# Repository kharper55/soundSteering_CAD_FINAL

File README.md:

All CAD pdfs and RAW files from KiCAD6 and some nice pin mapping references + block diagrams. Custom symbol and footprint library (not provided) needed to rebuild Gerbers (provided as-is). 

Contains schematic, PCB, BOM (entire KiCAD project + PDF prints) and Gerber files for 3x 4 layer mixed signal PCBs. KiCAD project has since seen edits in silkscreen and rectifying some issues with DNP parts.

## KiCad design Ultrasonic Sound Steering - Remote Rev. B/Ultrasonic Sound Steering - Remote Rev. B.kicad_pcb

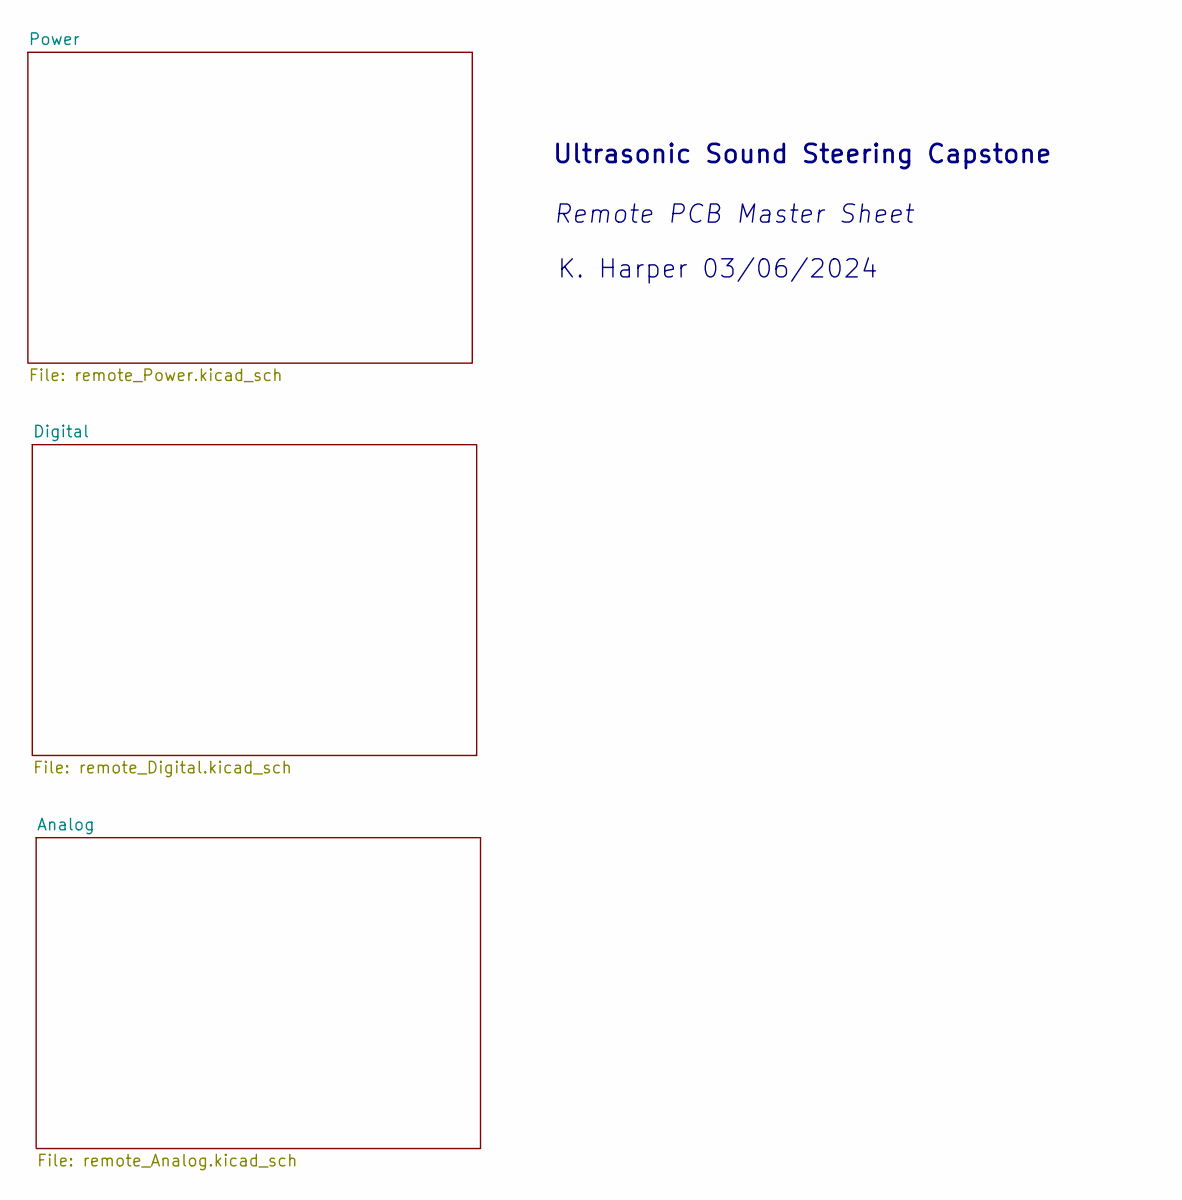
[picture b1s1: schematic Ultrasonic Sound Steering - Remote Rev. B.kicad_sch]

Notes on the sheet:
Remote PCB Master Sheet
K. Harper 03/06/2024
Ultrasonic Sound Steering Capstone

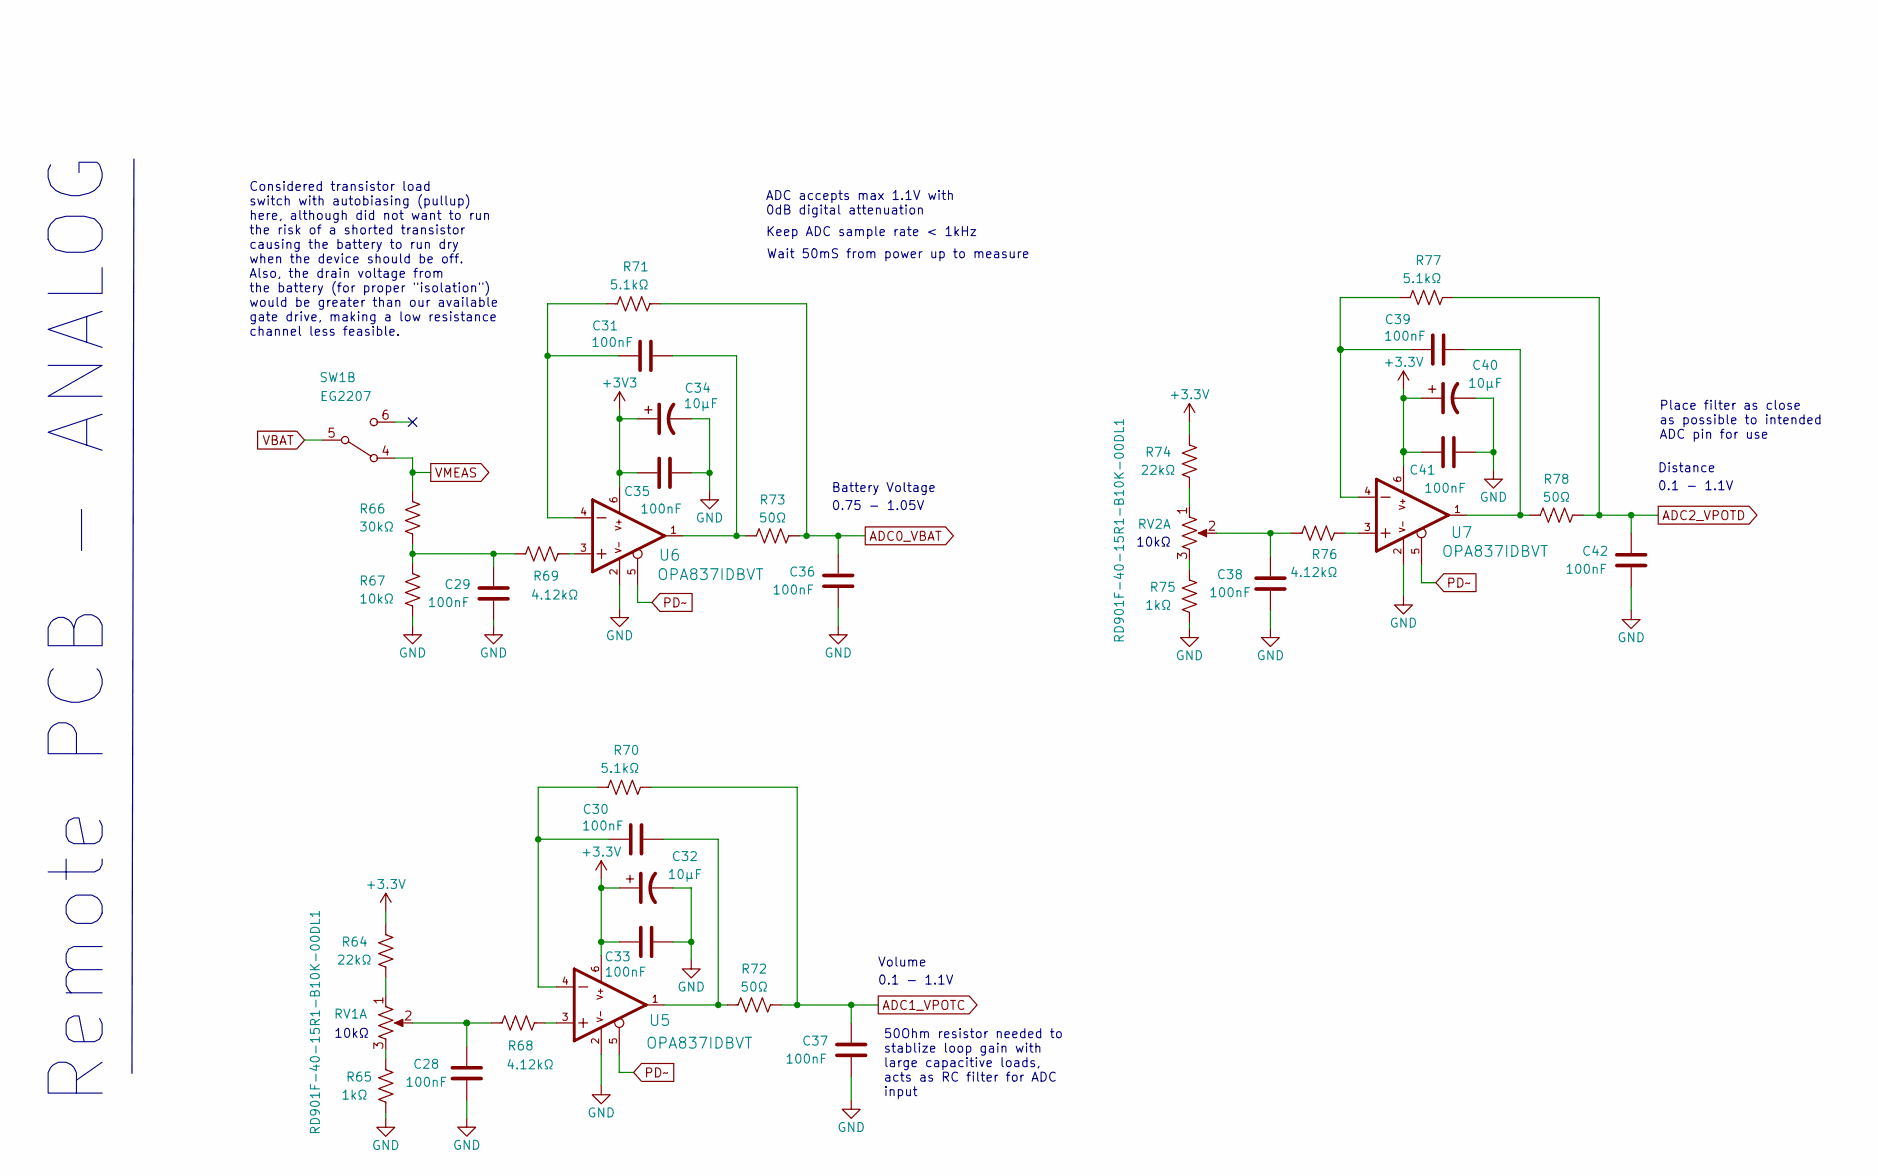
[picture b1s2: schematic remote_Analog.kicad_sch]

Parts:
C28, C29, C30, C31, C33, C35, C36, C37, C38, C39, C41, C42: 100nF; C_0603_1608Metric
C32, C34, C40: 10µF; C_TANT_1608-10
R64, R74: 22kΩ; R_0603_1608Metric
R65, R75: 1kΩ; R_0603_1608Metric
R66: 30kΩ; R_0603_1608Metric
R67: 10kΩ; R_0603_1608Metric
R68, R69, R76: 4.12kΩ; R_0603_1608Metric
R70, R71, R77: 5.1kΩ; R_0603_1608Metric
R72, R73, R78: 50Ω; R_0603_1608Metric
RV1, RV2: RD901F-40-15R1-B10K-00DL1; Potentiometer_Alps_RK09L_Single_Vertical
SW1: EG2207; SW_EG2207
U5, U6, U7: OPA837IDBVT; IC_SOT23-6

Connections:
ADC1_VPOTC: C37.2, R70.2, R72.2; also elsewhere on the board
ADC2_VPOTD: C42.2, R77.2, R78.2; also elsewhere on the board
GND: C28.1, C29.1, C32.2, C33.2, C34.2, C35.2, C36.1, C37.1, C38.1, C40.2, C41.2, C42.1, R65.2, R67.2, R75.2, U5.2, U6.2, U7.2; also elsewhere on the board
unnamed: C28.2, R68.1, RV1.2
unnamed: C29.2, R66.2, R67.1, R69.1
unnamed: C30.1, R70.1, U5.4
unnamed: C30.2, R72.1, U5.1
unnamed: C31.1, R71.1, U6.4
unnamed: C31.2, R73.1, U6.1
unnamed: C38.2, R76.1, RV2.2
unnamed: C39.1, R77.1, U7.4
unnamed: C39.2, R78.1, U7.1
unnamed: R64.2, RV1.1
unnamed: R65.1, RV1.3
unnamed: R68.2, U5.3
unnamed: R69.2, U6.3
unnamed: R74.2, RV2.1
unnamed: R75.1, RV2.3
unnamed: R76.2, U7.3
PD~: U5.5, U6.5, U7.5; also elsewhere on the board
VBAT: SW1.5; also elsewhere on the board
VMEAS: R66.1, SW1.4; also elsewhere on the board

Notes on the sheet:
Wait 50mS from power up to measure
Distance
Remote PCB - ANALOG
Place filter as close as possible to intended ADC pin for use
0.75 - 1.05V
Keep ADC sample rate < 1kHz
ADC accepts max 1.1V with 0dB digital attenuation
Volume
50Ohm resistor needed to stablize loop gain with large capacitive loads, acts as RC filter for ADC input
10kΩ
Battery Voltage
0.1 - 1.1V
Considered transistor load switch with autobiasing (pullup) here, although did not want to run the risk of a shorted transistor causing the battery to run dry when the device should be off. Also, the drain voltage from the battery (for proper "isolation") would be greater than our available gate dr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

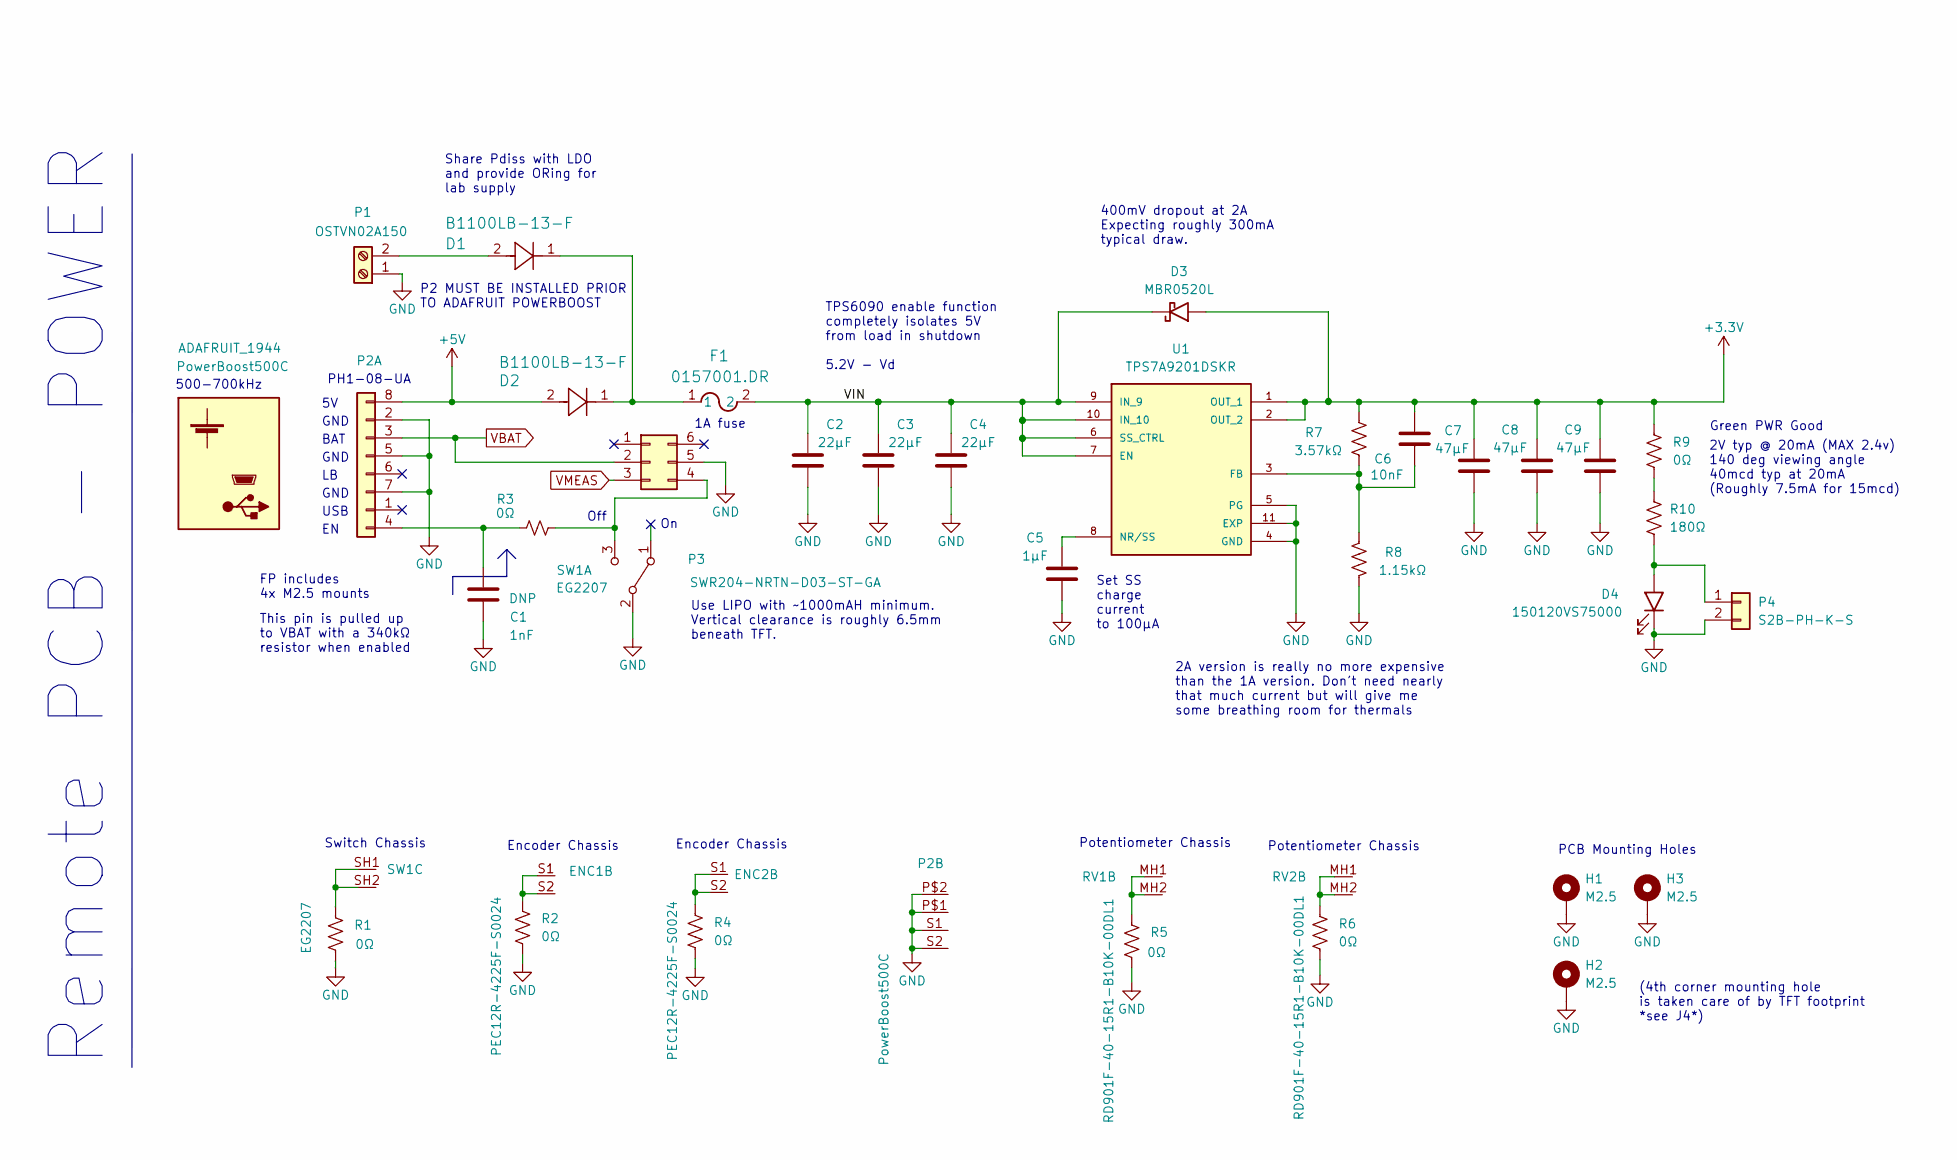
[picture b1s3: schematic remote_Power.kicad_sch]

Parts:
C1: 1nF; C_0603_1608Metric
C2, C3, C4: 22µF; C_0603_1608Metric
C5: 1µF; C_0603_1608Metric
C6: 10nF; C_0603_1608Metric
C7, C8, C9: 47µF; C_0603_1608Metric
D1, D2: B1100LB-13-F; D_SMB
D3: MBR0520L; D_SOD_123
D4: 150120VS75000; D_1206
ENC1, ENC2: PEC12R-4225F-S0024; XDCR_PEC12R-4215F-S0024
F1: 0157001.DR; FUSE_0157_SMD2
H1, H2, H3: M2.5; MountingHole_3.2mm_M3_DIN965_Pad_TopBottom
MODULE1: ADAFRUIT_1944
P1: OSTVN02A150; PinHeader_1x02_P2.54mm_Vertical
P2: PowerBoost500C; DB_POWERBOOST500C
P3: SWR204-NRTN-D03-ST-GA; sullinsSWR204
P4: S2B-PH-K-S; JST_PH_S2B-PH-K_1x02_P2.00mm_Horizontal
R1, R2, R3, R4, R5, R6, R9: 0Ω; R_0603_1608Metric
R7: 3.57kΩ; R_0603_1608Metric
R8: 1.15kΩ; R_0603_1608Metric
R10: 180Ω; R_0603_1608Metric
RV1, RV2: RD901F-40-15R1-B10K-00DL1; Potentiometer_Alps_RK09L_Single_Vertical
SW1: EG2207; SW_EG2207
U1: TPS7A9201DSKR; IC_SON-10_EP_2.5X2.5; PARTREV December 2016

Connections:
+5V: D2.2, P2.8
/Power/VIN: C2.2, C3.2, C4.2, D3.1 (K), F1.2, U1.6 (SS_CTRL), U1.7 (EN), U1.9 (IN_9), U1.10 (IN_10)
GND: C1.2, C2.1, C3.1, C4.1, C5.1, C7.1, C8.1, C9.1, D4.1 (K), H1.1, H2.1, H3.1, P1.1, P2.2, P2.5, P2.7, P2.P$1, P2.P$2, P2.S1 (M1), P2.S2 (M2), P3.5, P4.2, R1.2, R2.2, R4.2, R5.2, R6.2, R8.1, SW1.2, U1.4 (GND), U1.5 (PG), U1.11 (EXP), U1.12, U1.13, U1.14, U1.15; also elsewhere on the board
unnamed: C1.1, P2.4, R3.1
unnamed: C5.2, U1.8 (NR/SS)
unnamed: C6.1, R7.1, R8.2, U1.3 (FB)
unnamed: D1.1, D2.1, F1.1
unnamed: D1.2, P1.2
unnamed: D4.2 (A), P4.1, R10.2
unnamed: ENC1.S1 (MP1), ENC1.S2 (MP2), R2.1
unnamed: ENC2.S1 (MP1), ENC2.S2 (MP2), R4.1
unnamed: P3.4, R3.2, SW1.3
unnamed: R1.1, SW1.SH1, SW1.SH2
unnamed: R5.1, RV1.MH1 (MH2), RV1.MH2 (MH1)
unnamed: R6.1, RV2.MH1 (MH2), RV2.MH2 (MH1)
unnamed: R9.2, R10.1
VBAT: P2.3, P3.2; also elsewhere on the board
VMEAS: P3.3; also elsewhere on the board

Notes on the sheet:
PWR Good
TPS6090 enable function completely isolates 5V from load in shutdown 5.2V - Vd
Share Pdiss with LDO and provide ORing for lab supply
Switch Chassis
GND
500-700kHz
Remote PCB - POWER
This pin is pulled up to VBAT with a 340kΩ resistor when enabled
Set SS charge current to 100µA
BAT
PCB Mounting Holes
P2 MUST BE INSTALLED PRIOR TO ADAFRUIT POWERBOOST
2A version is really no more expensive than the 1A version. Don't need nearly that much current but will give me some breathing room for thermals
Off
USB
Encoder Chassis
(4th corner mounting hole is taken care of by TFT footprint *see J4*)
Green
PH1-08-UA
FP includes 4x M2.5 mounts
400mV dropout at 2A Expecting roughly 300mA typical draw.
Use LIPO with ~1000mAH minimum. Vertical clearance is roughly 6.5mm beneath TFT.
Potentiometer Chassis
2V typ @ 20mA (MAX 2.4v) 140 deg viewing angle 40mcd typ at 20mA (Roughly 7.5mA for 15mcd)
1A fuse

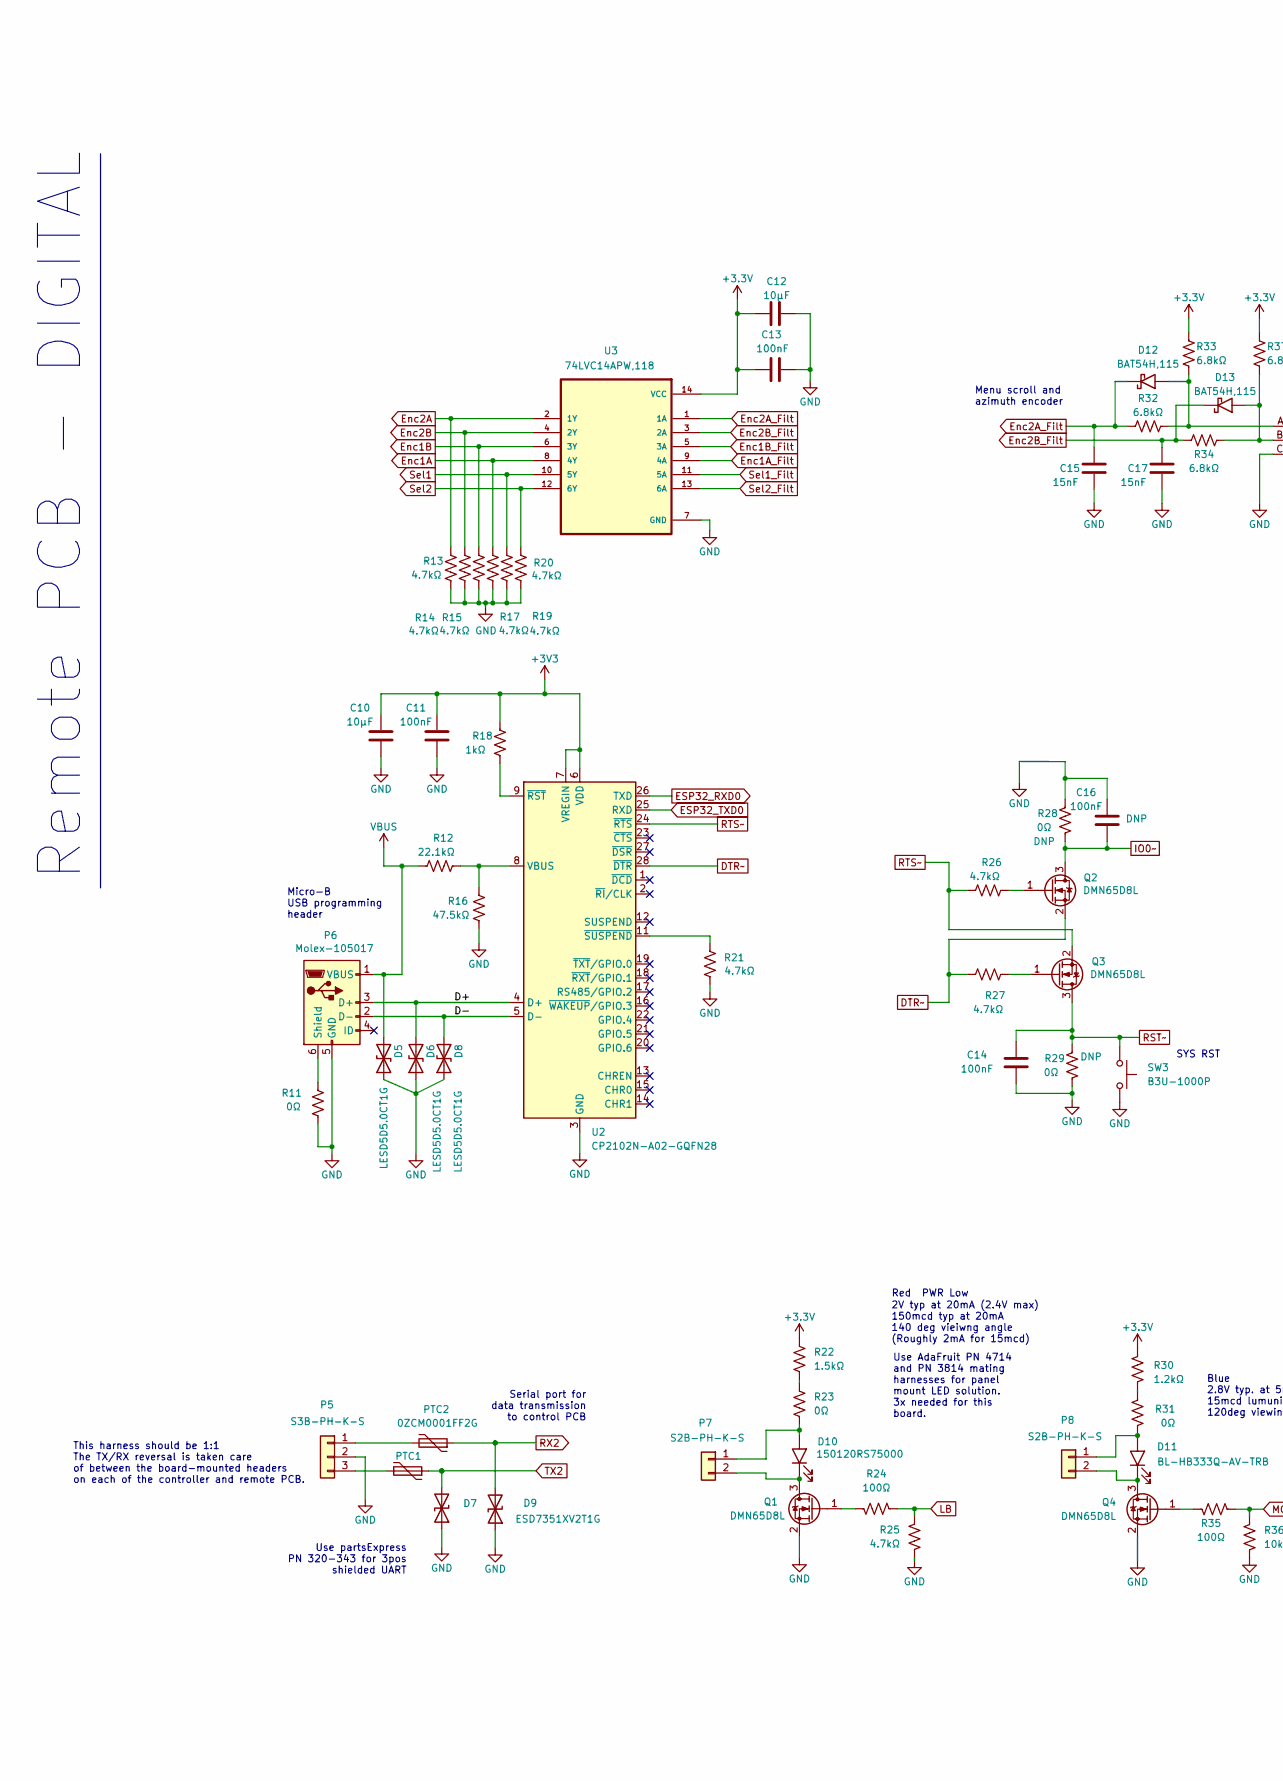
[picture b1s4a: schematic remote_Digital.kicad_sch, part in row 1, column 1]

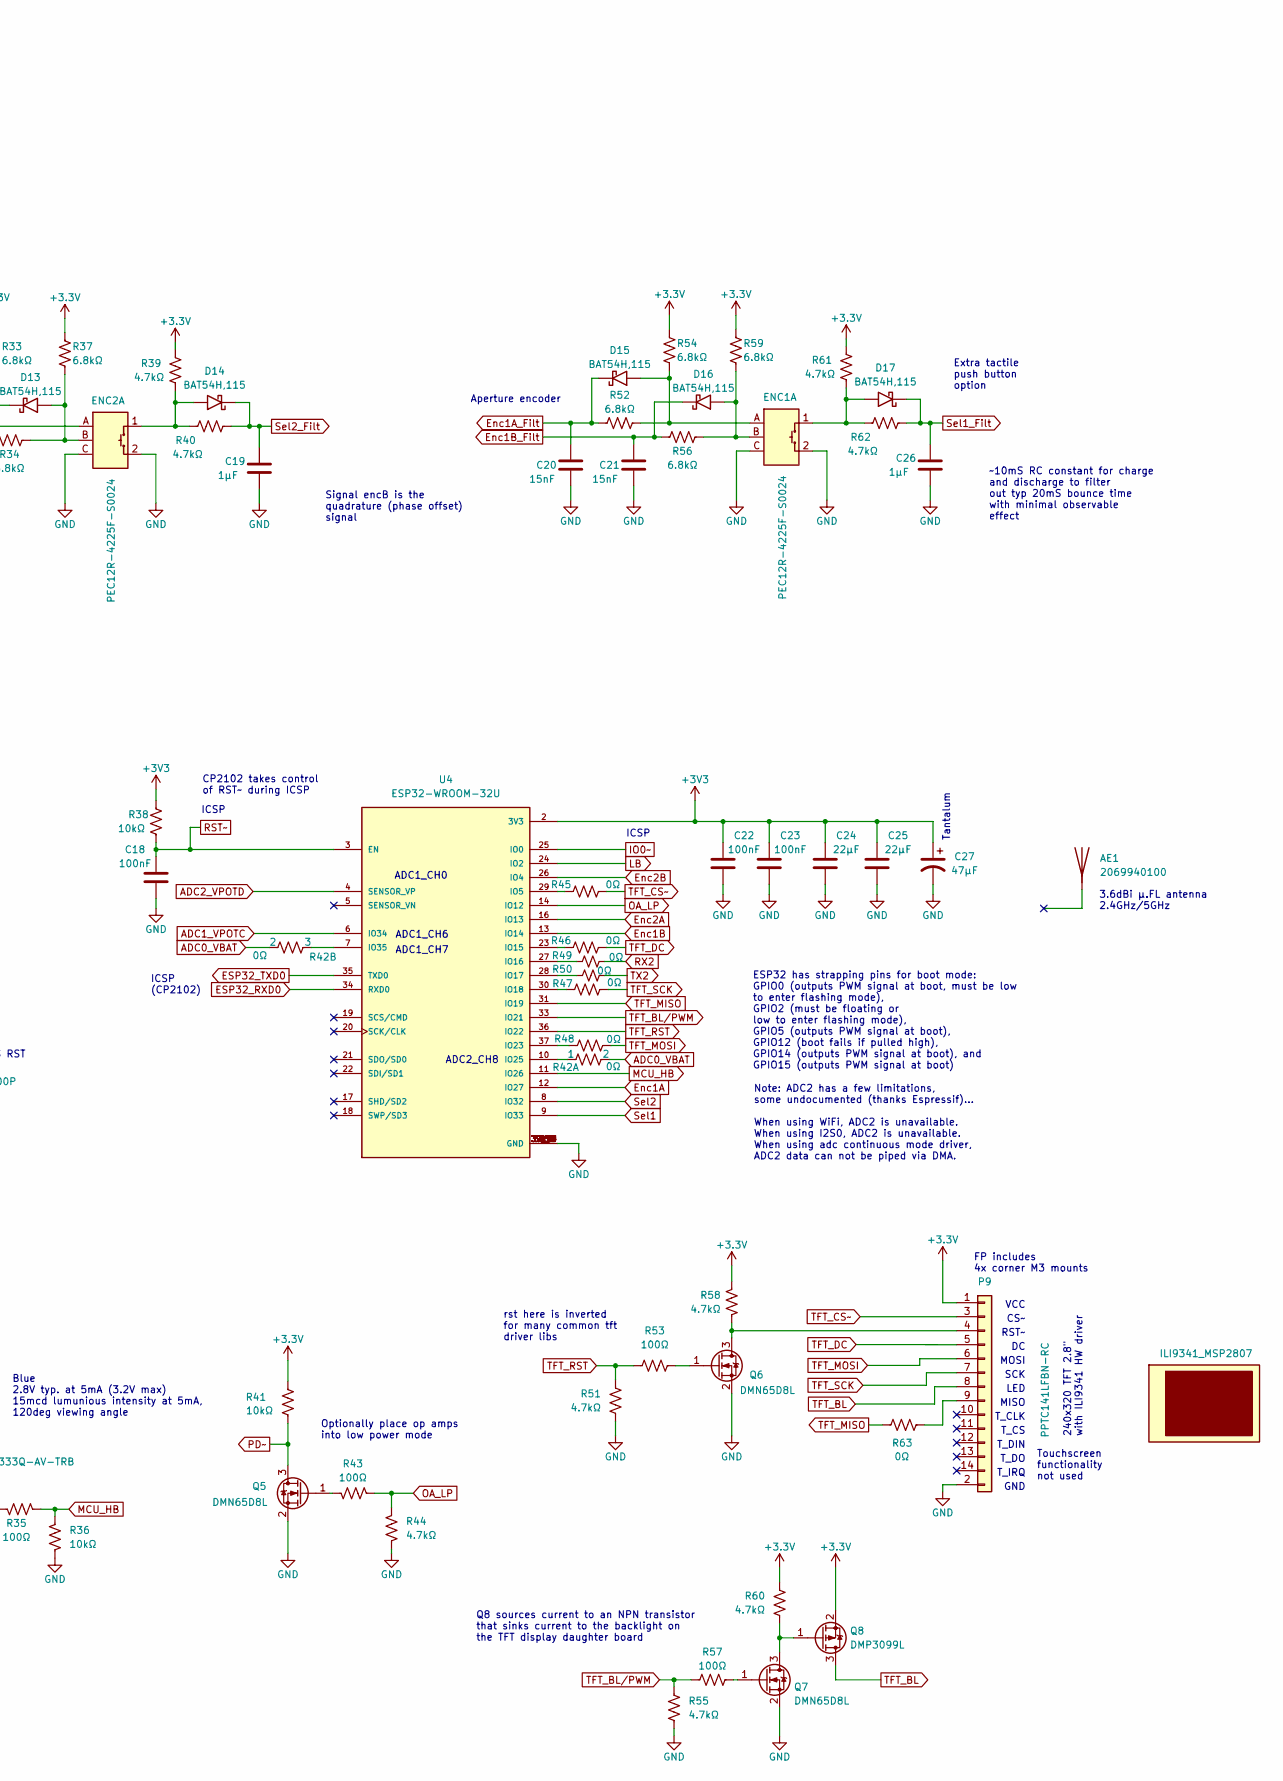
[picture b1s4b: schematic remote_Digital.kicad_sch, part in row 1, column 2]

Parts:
AE1: 2069940100
C10, C12: 10µF; C_0603_1608Metric
C11, C13, C14, C16, C18, C22, C23: 100nF; C_0603_1608Metric
C15, C17, C20, C21: 15nF; C_0603_1608Metric
C19, C26: 1µF; C_0603_1608Metric
C24, C25: 22µF; C_0603_1608Metric
C27: 47µF; C_TANT_3216-18_Kemet-A
D5, D6, D8: LESD5D5.0CT1G; D_SOD_523
D7, D9: ESD7351XV2T1G; D_SOD_523
D10: 150120RS75000; D_1206
D11: BL-HB333Q-AV-TRB; D_1206
D12, D13, D14, D15, D16, D17: BAT54H,115; D_SOD_123F
ENC1, ENC2: PEC12R-4225F-S0024; XDCR_PEC12R-4215F-S0024
MODULE2: ILI9341_MSP2807
P5: S3B-PH-K-S; CON_1053131103
P6: Molex-105017; USB_Micro-B_Molex-105017-0001
P7, P8: S2B-PH-K-S; JST_PH_S2B-PH-K_1x02_P2.00mm_Horizontal
P9: PPTC141LFBN-RC; QD-TFT2803
PTC1, PTC2: 0ZCM0001FF2G; R_0603_1608Metric
Q1, Q2, Q3, Q4, Q5, Q6, Q7: DMN65D8L; T_SOT23
Q8: DMP3099L; T_SOT23
R11, R23, R28, R29, R31, R45, R46, R47, R48, R49, R50, R63: 0Ω; R_0603_1608Metric
R12: 22.1kΩ; R_0603_1608Metric
R13, R14, R15, R17, R19, R20, R21, R25, R26, R27, R39, R40, R44, R51, R55, R58, R60, R61, R62: 4.7kΩ; R_0603_1608Metric
R16: 47.5kΩ; R_0603_1608Metric
R18: 1kΩ; R_0603_1608Metric
R22: 1.5kΩ; R_0603_1608Metric
R24, R35, R43, R53, R57: 100Ω; R_0603_1608Metric
R30: 1.2kΩ; R_0603_1608Metric
R32, R33, R34, R37, R52, R54, R56, R59: 6.8kΩ; R_0603_1608Metric
R36, R38, R41: 10kΩ; R_0603_1608Metric
R42: 0Ω; R_0603_JUMPER
SW3: B3U-1000P; SW_SPST_B3U-1000P
U2: CP2102N-A02-GQFN28; IC_QFN-28_EP_5x5
U3: 74LVC14APW,118; IC_TSSOP-14_0.65P; MPN 74LVC14APW,118
U4: ESP32-WROOM-32U; IC_ESP32-WROOM32U; PARTREV 1.9

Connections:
/Digital/D+: D6.2 (A2), P6.3 (D+), U2.4 (D+)
/Digital/D-: D8.2 (A2), P6.2 (D-), U2.5 (D-)
ADC1_VPOTC: U4.6 (IO34); also elsewhere on the board
ADC2_VPOTD: U4.4 (SENSOR_VP); also elsewhere on the board
DTR~: Q2.2 (S), R27.1, U2.28 (~DTR)
ESP32_RXD0: U2.26 (TXD), U4.34 (RXD0)
ESP32_TXD0: U2.25 (RXD), U4.35 (TXD0)
Enc1A: R17.1, U3.8 (4Y), U4.12 (IO27)
Enc1A_Filt: C20.1, D15.1 (K), R52.1, U3.9 (4A)
Enc1B: R15.1, U3.6 (3Y), U4.13 (IO14)
Enc1B_Filt: C21.1, D16.1 (K), R56.1, U3.5 (3A)
Enc2A: R13.1, U3.2 (1Y), U4.16 (IO13)
Enc2A_Filt: C15.1, D12.1 (K), R32.1, U3.1 (1A)
Enc2B: R14.1, U3.4 (2Y), U4.26 (IO4)
Enc2B_Filt: C17.1, D13.1 (K), R34.1, U3.3 (2A)
GND: C10.1, C11.1, C12.1, C13.2, C14.1, C15.2, C16.2, C17.2, C18.1, C19.2, C20.2, C21.2, C22.1, C23.1, C24.1, C25.1, C26.2, C27.2, D5.1 (A1), D6.1 (A1), D7.1 (A1), D8.1 (A1), D9.1 (A1), ENC1.2, ENC1.C, ENC2.2 (S2), ENC2.C, P5.2, P6.5 (GND), P9.2, Q1.2 (S), Q4.2 (S), Q5.2 (S), Q6.2 (S), Q7.2 (S), R11.1, R13.2, R14.2, R15.2, R16.2, R17.2, R19.2, R20.2, R21.2, R25.2, R28.2, R29.1, R36.2, R44.2, R51.2, R55.2, SW3.2, U2.3 (GND), U2.29 (GND), U3.7 (GND), U4.1 (GND), U4.15 (GND), U4.38 (GND), U4.39_1 (GND), U4.39_2 (GND), U4.39_3 (GND), U4.39_4 (GND), U4.39_5 (GND), U4.39_6 (GND), U4.39_7 (GND), U4.39_8 (GND), U4.39_9 (GND), U4.39_10 (GND), U4.39_11 (GND), U4.39_12 (GND), U4.39_13 (GND), U4.39_14 (GND), U4.39_15 (GND), U4.39_16 (GND), U4.39_17 (GND), U4.39_18 (GND), U4.39_19 (GND), U4.39_20 (GND), U4.39_21 (GND); also elsewhere on the board
IO0~: C16.1, Q2.3 (D), R28.1, U4.25 (IO0)
LB: R24.1, R25.1, U4.24 (IO2)
MCU_HB: R35.1, R36.1, U4.11 (IO26)
unnamed: D10.1 (K), P7.2, Q1.3 (D)
unnamed: D10.2 (A), P7.1, R23.2
unnamed: D11.1 (K), P8.2, Q4.3 (D)
unnamed: D11.2 (A), P8.1, R31.2
unnamed: D12.2 (A), ENC2.A, R32.2, R33.2
unnamed: D13.2 (A), ENC2.B, R34.2, R37.2
unnamed: D14.2 (A), ENC2.1 (S1), R39.2, R40.1
unnamed: D15.2 (A), ENC1.A, R52.2, R54.2
unnamed: D16.2 (A), ENC1.B, R56.2, R59.2
unnamed: D17.2 (A), ENC1.1, R61.2, R62.1
unnamed: P5.1, PTC2.2
unnamed: P5.3, PTC1.2
unnamed: P6.6 (Shield), R11.2
unnamed: P9.4, Q6.3 (D), R58.2
unnamed: P9.9, R63.2
unnamed: Q1.1 (G), R24.2
unnamed: Q2.1 (G), R26.2
unnamed: Q3.1 (G), R27.2
unnamed: Q4.1 (G), R35.2
unnamed: Q5.1 (G), R43.2
unnamed: Q6.1 (G), R53.2
unnamed: Q7.1 (G), R57.2
unnamed: Q7.3 (D), Q8.1, R60.1
unnamed: R12.1, R16.1, U2.8 (VBUS)
unnamed: R18.2, U2.9 (~RST)
unnamed: R21.1, U2.11 (~SUSPEND)
unnamed: R22.2, R23.1
unnamed: R30.2, R31.1
unnamed: R42.1, U4.10 (IO25)
unnamed: R45.1, U4.29 (IO5)
unnamed: R46.1, U4.23 (IO15)
unnamed: R47.1, U4.30 (IO18)
unnamed: R48.1, U4.37 (IO23)
unnamed: R49.1, U4.27 (IO16)
unnamed: R50.1, U4.28 (IO17)
OA_LP: R43.1, R44.1, U4.14 (IO12)
PD~: Q5.3 (D), R41.2; also elsewhere on the board
RST~: C14.2, C18.2, Q3.3 (D), R29.2, R38.2, SW3.1, U4.3 (EN)
RTS~: Q3.2 (S), R26.1, U2.24 (~RTS)
RX2: D9.2 (A2), PTC2.1, R49.2
Sel1: R19.1, U3.10 (5Y), U4.9 (IO33)
Sel1_Filt: C26.1, D17.1 (K), R62.2, U3.11 (5A)
Sel2: R20.1, U3.12 (6Y), U4.8 (IO32)
Sel2_Filt: C19.1, D14.1 (K), R40.2, U3.13 (6A)
TFT_BL: P9.8, Q8.3
TFT_BL/PWM: R55.1, R57.1, U4.33 (IO21)
TFT_CS~: P9.3, R45.2
TFT_DC: P9.5, R46.2
TFT_MISO: R63.1, U4.31 (IO19)
TFT_MOSI: P9.6, R48.2
TFT_RST: R51.1, R53.1, U4.36 (IO22)
TFT_SCK: P9.7, R47.2
TX2: D7.2 (A2), PTC1.1, R50.2
VBUS: D5.2 (A2), P6.1 (VBUS), R12.2

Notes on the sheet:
T_CLK
CP2102 takes control of RST~ during ICSP
Blue 2.8V typ. at 5mA (3.2V max) 15mcd lumunious intensity at 5mA, 120deg viewing angle
VCC
Signal encB is the quadrature (phase offset) signal
Use AdaFruit PN 4714 and PN 3814 mating harnesses for panel mount LED solution. 3x needed for this board.
3.6dBi µ.FL antenna 2.4GHz/5GHz
MOSI
Q8 sources current to an NPN transistor that sinks current to the backlight on the TFT display daughter board
Remote PCB - DIGITAL
Note: ADC2 has a few limitations, some undocumented (thanks Espressif)... When using WiFi, ADC2 is unavailable. When using I2S0, ADC2 is unavailable. When using adc continuous mode driver, ADC2 data can not be piped via DMA.
CS~
T_IRQ
Micro-B USB programming header
ICSP
Use partsExpress PN 320-343 for 3pos shielded UART
T_DIN
Red
ESP32 has strapping pins for boot mode: GPIO0 (outputs PWM signal at boot, must be low to enter flashing mode), GPIO2 (must be floating or low to enter flashing mode), GPIO5 (outputs PWM signal at boot), GPIO12 (boot fails if pulled high), GPIO14 (outputs PWM signal at boot), and GPIO15 (outputs PW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
Aperture encoder
~10mS RC constant for charge and discharge to filter out typ 20mS bounce time with minimal observable effect
ADC1_CH6
SCK
SYS RST
ADC1_CH7
Extra tactile push button option
Touchscreen functionality not used
RST~
ADC1_CH0
Serial port for data transmission to control PCB
Optionally place op amps into low power mode
FP includes 4x corner M3 mounts
Tantalum
MISO
240x320 TFT 2.8" with ILI9341 HW driver
T_DO
ADC2_CH8
rst here is inverted for many common tft driver libs
Menu scroll and azimuth encoder
This harness should be 1:1 The TX/RX reversal is taken care of between the board-mounted headers on each of the controller and remote PCB.

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
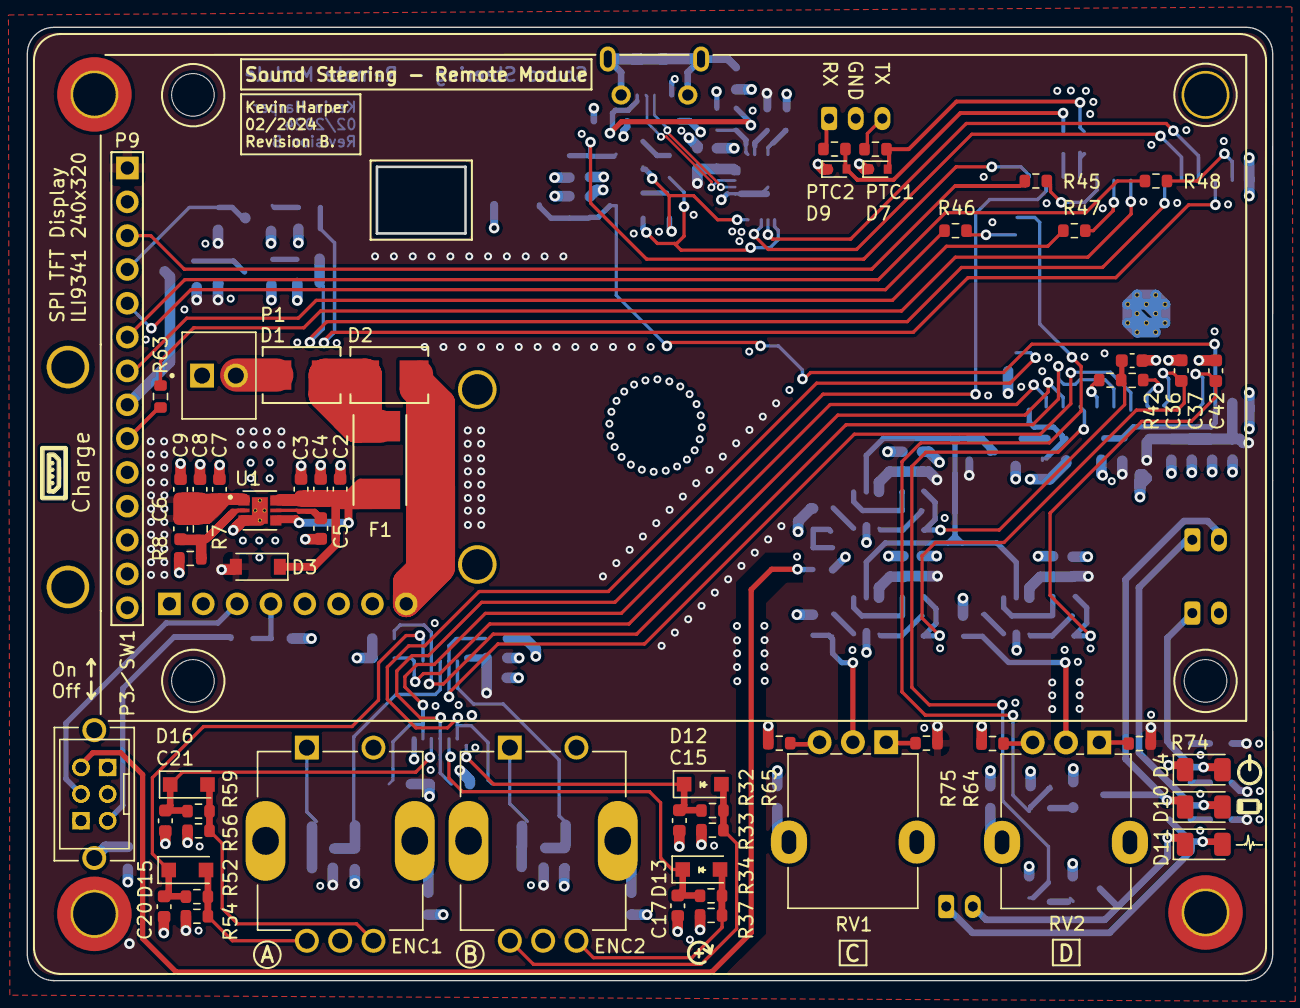
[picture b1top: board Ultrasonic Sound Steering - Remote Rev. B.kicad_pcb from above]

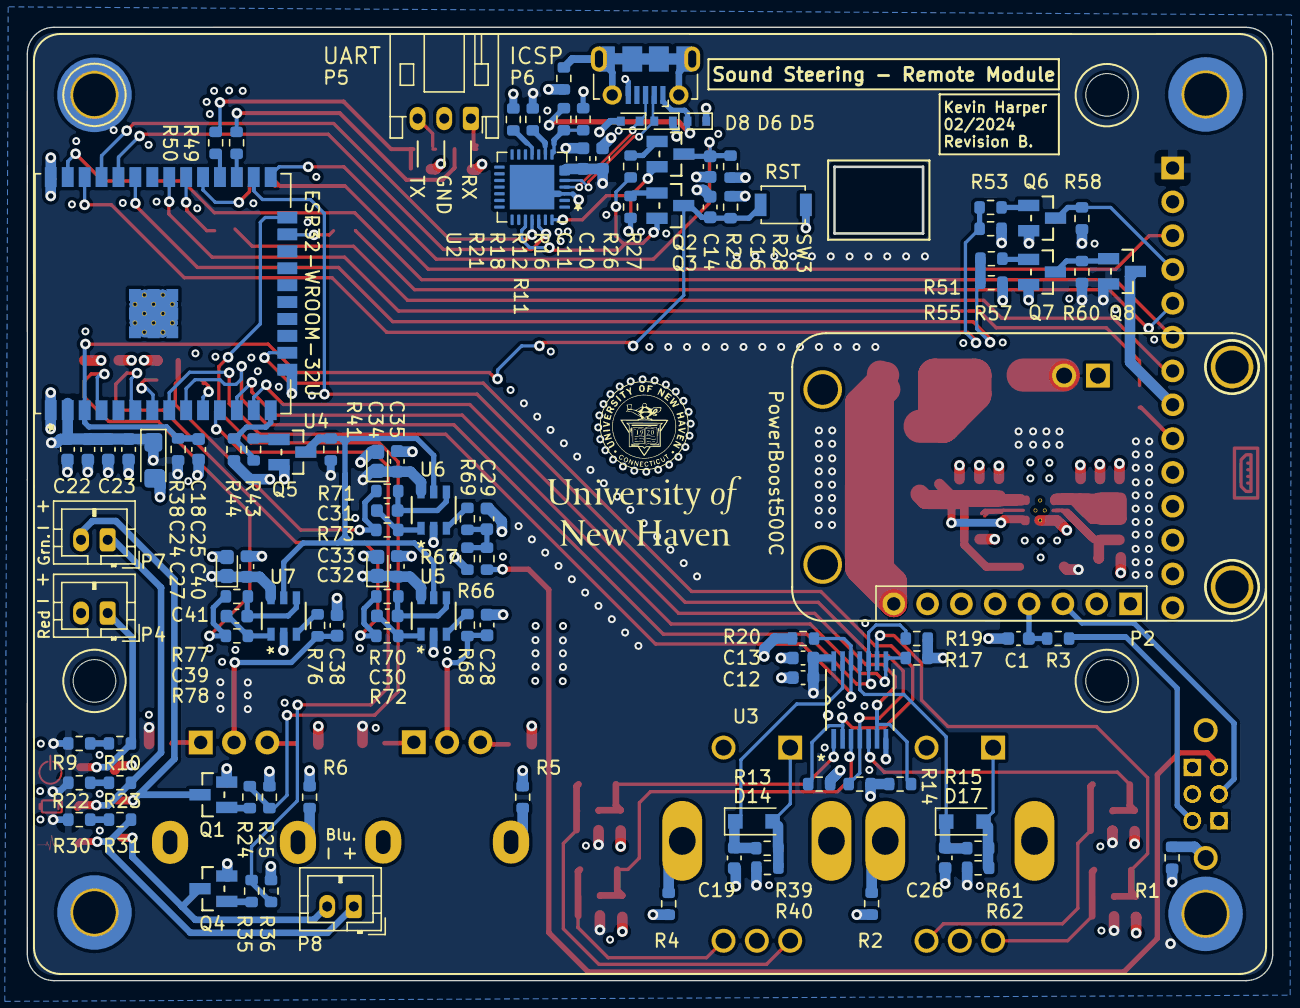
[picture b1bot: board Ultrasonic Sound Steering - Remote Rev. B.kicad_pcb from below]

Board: 4 copper layers, 93.4 x 71.5 mm, 173 parts (111 on the bottom side), 109 nets.

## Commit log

2024-05-02 words
2024-06-07 PDF prints of all schematic files
    KiCAD 6
2024-06-07 Various info pertaining to the FPGA design
2024-06-30 System hardware block diagram
    A better depiction of the system in its' entirety
2024-06-30 A system-level block diagram
2024-06-30 FSM Diagram
    A state machine depiction which describes the exact implementation, despite having some less meaningful state bubbles.
